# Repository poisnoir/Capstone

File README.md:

# EM AccuBot — Team 25 (ELEC/COEN 490)

FPGA-based electromagnetic motion controller for precision teleoperation.
A pen-shaped 5-DOF hand controller drives a micro-positioning follower at
20:1–1000:1 (default 100:1) with tremor filtering (6–12 Hz → ≥20 dB),
targeting ≤25 µm tool error at 100:1.

**Agents: read `AGENTS.md` first.** It is the authoritative handoff.

## Start here (30 minutes)

1. `contract/README.md` — the shared contract, current version and change process.
2. `contract/system_contract.md` — SC-01…SC-10 and decisions D1–D4.
3. `contract/decisions_log.md` — every locked decision with its source.
4. Your team's `AGENTS.md` + `README.md`.
5. `docs/phase2/design_order.md` — the stage gates (SC-0 → FG-1 → … → INT-7).

If you only read one thing before building: **`contract/system_contract.md`**.
If you are about to change an interface: read `contract/README.md` first.

## Teams and ownership

| Team | People | Owns |
|---|---|---|
| FPGA | Kevin, William (+ Amirmohammad for filter/scaling) | `fpga/` — DDS, ADC capture, demod, LM/TRF solver, filter/scaling |
| Hardware | Tung | `hardware/` — BRD-01, FG-01, pen, mechanical, BOMs |
| Robot arm | Tristan, Joyal | separate arm repo (Pico firmware, motor config, mechanics); `robot-arm/` here is the integration stub |
| Integration / contract | leads + contract owner | `contract/`, `docs/`, `tools/`, cross-team gates |

Ownership is expressed in `CODEOWNERS`; the contract is the one shared write
surface. Team folders are owned by their team.

## Repo map

```
contract/     canonical contract: SC, decisions, ICDs, requirements
fpga/         HDL/HLS: DDS, ADC sync, demod, LM/TRF solver
hardware/     BRD-01, FG-01, pen, mechanical, BOMs
robot-arm/    integration stub + handshake kit for the separate arm repo
software/     host tools: logging, calibration, viz (no pose solve)
simulations/  field/solver/filter sims (.raw outputs are gitignored)
docs/         phase1/, phase2/, handoff/, reference/, meetings/, setup/
tools/        checkers, manifest generator, extract script
.github/      issue/PR templates + CI
```

## The contract is versioned

- Current version: `contract/VERSION` (1.1.0; tag `contract-v1.1.0` pending review).
- On every push to `main` that changes `contract/`, CI publishes
  `contract-vX.Y.Z.zip` + `contract-vX.Y.Z.json` as a GitHub Release, plus a
  rolling `contract-latest`.
- The arm repo pins a version and pulls the release with a read-only token; see
  `robot-arm/README.md`.
- A contract change requires a `contract-change` issue, a PR, two approvals, a
  `VERSION` bump and a `CHANGELOG.md` entry.

## References are not in the repo

Third-party PDFs, datasheets and the vendor snapshot are **not committed**
(copyright and size). Every excluded file has an entry in
`docs/reference/MANIFEST.md` saying what it is, which docs use it, and how to
obtain it. Run `python3 tools/check_references.py` to verify coverage.

## Status

Phase 2 design. Full-FPGA pose locked 2026-10-12; one-board BRD-01 and PS-less
Artix-7 locked 2026-10-28; M16 DAC/filter selected 2026-10-27; arm-only STOP
(#30) and power tree v2 (#31) recorded 2026-11-25 (contract 1.1.0 pending tag).
See `contract/decisions_log.md` for the full record.

## Working rules

- `main` is integration; use short-lived branches (`fpga/…`, `hw/…`, `arm/…`,
  `contract/…`, `docs/…`) and open a PR.
- Run `python3 tools/check_doc_paths.py`, `python3 tools/check_references.py`
  and `python3 tools/contract_ci.py check` before pushing.
- Never commit a third-party PDF, datasheet, vendor file or `.raw` output.
- Do not edit `contract/` without a written deviation and a contract PR.

Details: `CONTRIBUTING.md`.

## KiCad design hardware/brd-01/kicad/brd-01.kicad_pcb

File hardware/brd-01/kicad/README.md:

# BRD-01 KiCad project

Open [brd-01.kicad_pro](brd-01.kicad_pro) in KiCad **10.0.8** with the
official 10.0.8 symbol and footprint libraries installed. The root schematic
contains five populated sheets. Signals that cross sheets
(`DRIVER_FAULT_N`, `BUCK_SYNC`) use hierarchical labels and
sheet pins on the root; power rails use power symbols. The connectors sheet
keeps the C2 (pen 1) and C4 (pen 2) harnesses as wired blocks.
Title block rev **0.1**; KiCad ERC reports **zero violations** on the full
hierarchy. The schematic is complete as an engineering draft and carries the
following release holds.

| Page | Sheet | Captured | Open |
|---|---|---|---|
| 2 | Power | Fused entry and corrected TVS polarity, unswitched +15 V_FUSED driver rail and hardware overcurrent latch retargeted to arm STOP, FPGA rail sequencing, +5VA regulator fed from +6 V via FL2, and the approved MGJ2D151515SC/LT3045EDD-1#TRPBF/LT3093EMSE#TRPBF ±12VA chain | Verify converter headroom and combined receiver and driver load against the 67 mA per-rail rating. Verify startup, rail load and dissipation against the 67 mA per-rail rating, clamp/release time, restart behavior and input protection. The 3.15 A fuse cartridge is a recorded deviation from the 3.00 A spec. |
| 3 | Driver | DAC80508, eight 60 kHz reconstruction filters, coil outputs and sense returns, sense summer, individual comparator test nets, nominal 253 mA prototype trip, nominal 280 mA peak LMH6321 clamps and a shared active-low fault output to the FPGA | Measure prototype command scaling and loop compensation with the coil and cable, verify coil-return midpoint impedance, LMH6321 clamp tolerance and thermal validation, trip threshold tolerance, and hardware latch pulse capture with arm STOP assertion. Confirm the summer scale and phase on the bench. **TRIP_REF is open:** the `R710` 52.3 kΩ / `R711` 10 kΩ divider gives ≈0.53 V, which is unreconciled with the sheet's "~253 mA at 3.3 V" trip note and "~280 mA nominal clamp" note; do not pick resistors before measuring (power_tree_v2.md §9). |
| 4 | Receiver | AD7768-4 in four-lane SPI-control configuration, ADR434 reference, Ch0 current sense, Ch1 pen 1, Ch2 pen 2 and Ch3 fixed-reference paths; three INA163UA (U104/U106/U107) and two dual ADA4940-2ACPZ (U105/U108), matching the BOM-to-CAD ±12VA load check | Ch2 gain equals Ch1's (closed); the Ch3 reference-coil front end stays in the board design but its parts are **DNP lines in the BOM** — not ordered or assembled. Verify ADC settling, reference buffer stability and phase matching. |
| 5 | FPGA | FTG256 ball assignments, QSPI and JTAG, shared clock, USB-UART and Pico signals | Verify timing, power and bypass allocation on the target device. Program FT231X CBUS2 for VBUS sensing and verify USB ESD and power-off behavior. |
| 6 | Connectors | Eight keyed FG headers, two pen panel connectors and JST harnesses, C2 (pen 1) and C4 (pen 2) as wired harness blocks, provisional JST GH headers for reference and Pico (J123.1 no-connect), plus USB-C with data and CC ESD clamps | Freeze pen and reference polarity and verify mating harnesses and shield termination. Approve USB shield bonding, enclosure fit and FG mating hardware. |

The BRD-01 draft uses the LTC1563-2 high-speed unity-gain application and the
LMH6321 single-supply ground-pin bias configuration. The driver and receiver
still need circuit review before layout. See [LTC1563-2 data sheet](https://www.analog.com/media/en/technical-documentation/data-sheets/156323fa.pdf)
and [LMH6321 data sheet](https://www.ti.com/lit/ds/symlink/lmh6321.pdf).

The 35T and 50T FTG256 tables agree on all 256 ball entries and the KiCad
symbol matches their pin names. The FPGA user signals and QSPI use 3.3 V
HR Banks 14, 15 and 34. Migration still needs implementation timing and
power verification. See the [XC7A35T table](https://download.amd.com/adaptive-socs-and-fpgas/developer/adaptive-socs-and-fpgas/package-pinout-files/a7packages/xc7a35tftg256pkg.txt)
and [XC7A50T table](https://download.amd.com/adaptive-socs-and-fpgas/developer/adaptive-socs-and-fpgas/package-pinout-files/a7packages/xc7a50tftg256pkg.txt).

The FPGA sheet and USB-C CC resistors use standard 0603 footprints for
the digital resistors and small bypass capacitors. The FPGA sheet uses
0805 for its 4.7 µF and 10 µF capacitors. These package assignments are
for layout. Confirm effective capacitance at the rail voltage when
selecting the exact capacitor part numbers.

The receiver and driver use 0603 for the small signal resistors and
capacitors, 0805 for 1 µF, 1206 for 10 µF, and 1 mm exposed pads for
driver probe points. Check resistor matching, capacitor dielectric and
effective capacitance when selecting orderable parts. Driver shunts
reserve provisional 2512 footprints pending part selection. The
coil-coupling capacitors provisionally use TDK CAA572X7R1E107M670LJ
and its series-specific footprint. C30 and
C282 have provisional 1000 µF Panasonic parts and footprints.

The power sheet assigns 0603 through 1210 footprints to regulator and
interlock passives. Qualify the two ±12VA output capacitor groups at
their actual bias voltage. Each LDO requires at least 10 µF effective
output capacitance. Place C5/C782 by U6 and C4/C783 by U2, with the
OUTS connection taken at the local capacitor pad.
[LT3045-1 datasheet](https://www.analog.com/media/en/technical-documentation/data-sheets/30451fa.pdf) ·
[LT3093 datasheet](https://www.analog.com/media/en/technical-documentation/data-sheets/lt3093.pdf)

L140 and L141 use Coilcraft XFL4020-222MEC with the KiCad
`Inductor_SMD:L_Coilcraft_XxL4020` footprint. TI lists the 2.2 µH
XFL4020-222 family for the TPS62130A and recommends the nominal
2.2 µH / 22 µF output filter combination. Check peak current and
transient response against the implemented FPGA rail loads.
[TPS62130A datasheet](https://www.ti.com/lit/ds/symlink/tps62130a.pdf) ·
[Coilcraft XFL4020-222](https://www.coilcraft.com/en-us/products/power/shielded-inductors/molded-inductor/xfl/xfl4020/xfl4020-222/)

### Sheet index

Capture is complete: every on-board symbol carries a value and a footprint.
The [BOM-to-CAD ledger](bom-to-cad.md) records the part evidence and the
release verification left on each lot. The rail authority is
[power_tree_v2.md](../../../docs/phase2/power_tree_v2.md) (decision #31); netlist
truth is [brd01_wiring_manifest.md](../../../docs/phase2/brd01_wiring_manifest.md).
[power-tree.md](power-tree.md) is the SUPERSEDED v1 record, not a rail authority.

| Page | Sheet | Contents |
|---|---|---|
| 2 | Power | Adapter entry, protection and EMI filter, unswitched `+15V_FUSED` driver rail, arm STOP latch, FPGA rail sequencing, +5VA from `+6V` and the approved ±12VA chain |
| 3 | Driver | DAC80508, eight 60 kHz filters, eight current loops, sense summer, comparators and open-drain fault bus |
| 4 | Receiver | AD7768-4, ADR434 reference, Ch0 current sense and Ch1–Ch3 sensor front ends |
| 5 | FPGA | FTG256 ball map, QSPI, JTAG, clock, USB-UART and Pico signals |
| 6 | Connectors | FG headers, pen panels, wired C2/C4 harness blocks, reference and Pico headers (J123.1 no-connect), USB-C and ESD |

No E-stop mushroom or relay remains on the power sheet. The board has no
panel E-stop: arm STOP comes from the host request or the hardware latch
(U752/U753/U755), and the +15 V_FUSED driver rail is unswitched. The pen
mini-XLR stays in the BOM as panel hardware.

### Library setup and checks

The project tables resolve `accubot` relative to `${KIPRJMOD}` at
[the shared hardware library](../../kicad/lib/). No global `accubot` table,
plugin, 3D model, or external CAD download is needed. To add more selected
parts in one batch, first check the official libraries against manufacturer
pin tables and package drawings, then curate only missing or incorrect
definitions directly in the shared library and update the ledger. Do not
commit downloaded libraries, datasheets, or per-part import projects.

From the repository root:

```bash
kicad-cli --version
kicad-cli sch erc --exit-code-violations -o /tmp/opencode/brd01-setup-erc.rpt hardware/brd-01/kicad/brd-01.kicad_sch
kicad-cli pcb drc --exit-code-violations -o /tmp/opencode/brd01-setup-drc.rpt hardware/brd-01/kicad/brd-01.kicad_pcb
mkdir -p /tmp/opencode/brd01-symbol-svg
kicad-cli sym export svg --output /tmp/opencode/brd01-symbol-svg hardware/kicad/lib/accubot.kicad_sym
```

KiCad ERC reports zero violations on rev 0.1. F1 carries the Schurter `0001.2509`
3.15 A time-delay cartridge as its MPN field; the 3.15 A rating is a recorded
deviation from the 3.00 A spec that the power owner accepted. The active-low
overcurrent bus reaches both the FPGA and the hardware latch (U752). The latch
clears on fault or supervisor reset; **`U753.5 (Q)` drives `/power/ARM_Q` →
`U755.2`**, and `U755.4` asserts `PICO_STOP_N` to the arm. **`U753.3 (~Q)` is the
intentional no-connect** (netlist proof:
`docs/phase2/brd01_wiring_manifest.md`, §5 consistency note 1). The field rail
stays live. The interlock still needs fault-injection validation. The prototype loop uses AC-coupled command scaling, a DC feedback path and provisional PI compensation. The summer uses a nominal gain of −2.000 from each input. Measure phase margin, tracking gain and polarity before operating the full array.
A nominal small-signal check used the captured 10 kΩ/100 nF sense path,
parallel 10 MΩ feedback and 330 kΩ/150 pF compensation, a one-pole 10 MHz
gain-bandwidth OPA192 model, an ideal buffer, and a legacy 70 µH + 2 Ω coil
approximation with
1 Ω shunt and 100 µF series coupling. The reduced closed-loop polynomial
has no right-half-plane poles. Its upper unity crossover is about 70 kHz
with about 80° nominal phase margin. The calculated shunt-current gain
from the filter output is 0.118 A/V at 20 kHz and 0.114 A/V at 34 kHz, so
150 mA RMS requires about 1.80–1.86 V peak at that node. Set initial DDS
amplitude below the nominal trip and trim against the shunt measurement.
Cable parasitics, real buffer and sense-amplifier dynamics, saturation,
capacitor ESR and rail transients are outside this reduced model. **Re-run this
check with the locked FG coil (79 µH / 2.9 Ω, decision #27) before using its
crossover numbers for component selection.**

The blank PCB
reports `invalid_outline` until layout adds a real outline. Put only the
released fabrication package in [fab](../fab/).

Setup verification also used a disposable project at the same relative paths
with only the standard global KiCad tables. All 19 units of the 15 curated
symbols loaded; removing the project symbol table produced 19 library errors.
Numbered symbol pins matched numbered footprint pads for the 8 official and
15 curated table pairings, including the JST pen header, and for the separate
ST TVS mapping. The follow-up ST and JST checks also verified pad geometry.

A later disposable schematic checked the JTAG symbol, panel mini-XLR, and
three draft symbols. All five resolved through the project table and
exported to the netlist. Only the panel mini-XLR and JTAG header appeared
in the fixture BOM.

Two disposable boards with outlines reported zero DRC violations: one with
`accubot:RECOM_RV-1515D_DIP24`, and one with `accubot:ST_SMBJ_DO-214AA_DS1283`
and the official JST pen header. These smoke checks verify library use, not
BRD-01 circuit capture, layout readiness, or pen harness qualification.

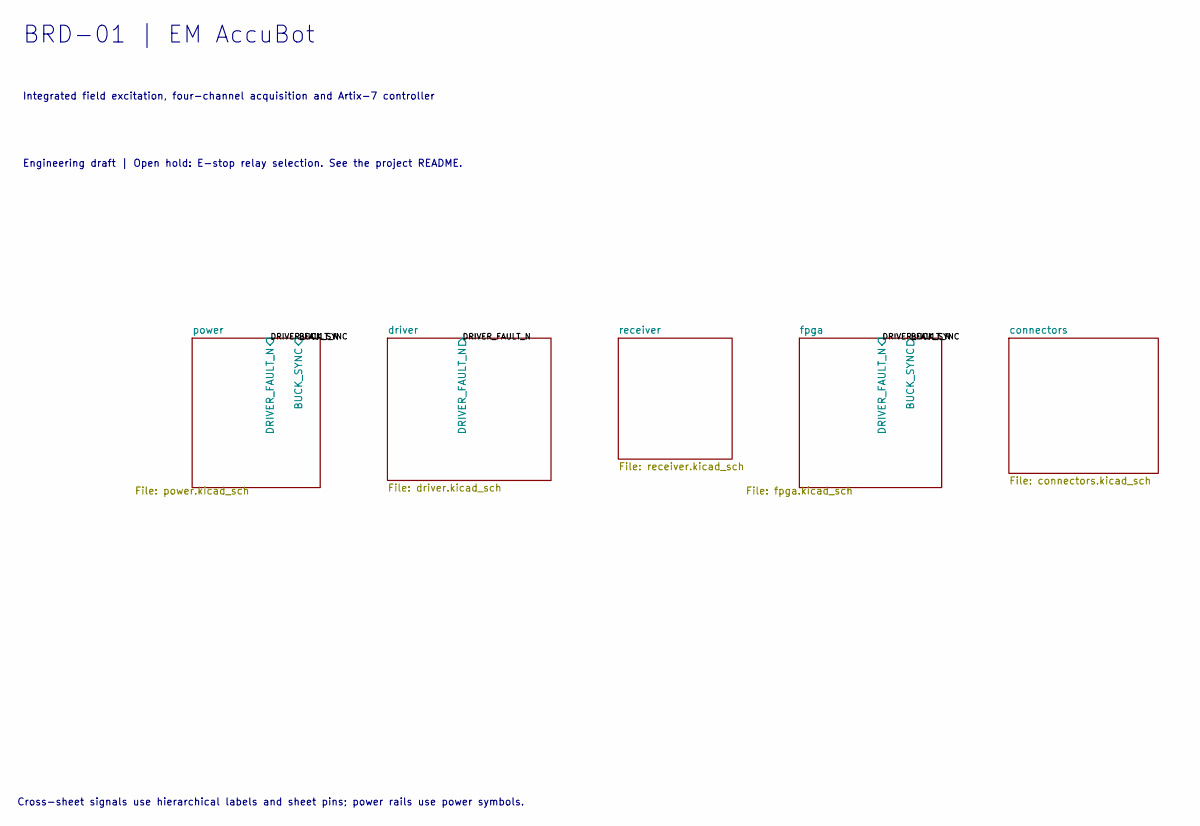
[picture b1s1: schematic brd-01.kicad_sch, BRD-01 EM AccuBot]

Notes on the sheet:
Cross-sheet signals use hierarchical labels and sheet pins; power rails use power symbols.
Engineering draft | Open hold: E-stop relay selection. See the project README.
BRD-01 | EM AccuBot
Integrated field excitation, four-channel acquisition and Artix-7 controller
